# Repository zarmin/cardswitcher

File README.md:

# Card switcher

In some cases physical switching of a smart card is required to operate / test a system, this project can change between multiple smart cards electronically.

The device can be managed via a USB interface (Serial bus over USB).

_The project is inspired by [Smart Card removinator project](https://github.com/nkinder/smart-card-removinator)._

# Hardware

The device is made up from 3 different components: card shield, card controller, card adapter

## Card shield

One device installation can use multiple card shields, one card shield can take one card. The maximum number of stackable card shields are 15 (or 16, but w/o a unselected option). These shields are vertically stacked pcb modules.

Every shield have a 4 bit address, which can be changed by a dip switch on the board (the space between the stacked modules are enough to change the address after it stacked with a tweezer). The controller can detect address collisions via a feedback resistor.

Card shields can't detect if they have an inserted card or not.

### Card shield schematics

### Card shield PCB

### Card shield photos

## Card controller

One device installation needs one controller. The controller will the base of the card shields.

The card controller can be controller (and powered) via mini USB. It connects to the card adapter with a ethernet cable (but not ethernet protocol of course).

It has an IC socket, initially designed to hold an ATMEGA168PA, with an Arduino software. The board also has a ISP connector to program the MCU.

### Card controller schematics

### Card controller PCB

### Card controller photos

## Card adapter

The card adapter is the _fake_ card, that goes into the real card slot.

### Card adapter PCB

### Card adapter photos

# Software

Software is in the mcu-software folder as an Arduino project. It can be uploaded via the USB interface or via the ISP. For the development the MiniCore Arduino board library used for the ATMega168IC (16 Mhz external clock; 168P / 168PA variant).

The software is checking the available card shield addresses upon boot and refuse to start (reboot loop with fast blinking of the activity LED) if an address collision is detected.
After the boot, it can be controlled via serial (via USB), by writing the addresses in ASCII (no newline required).

# Photos

_Installation with two card shield modules and cards_

## Example terminal communication

```
Serial init
Device found on address: 1
Device found on address: 2
Ready to use!
Address? >>
Set to address (no active device): 4
Address? >>
Set to address (active device): 1
Address? >>
Set to address (active device): 2
Address? >>
```

# Components

The EAGLE files are containing the required components numbers (extra component libraries also included).

Special (non common / passive) components are:
- card shield: 2x SN74HC4066DR Quadruple Bilateral Analog Switch
- card shield: 1x CD74HC85M CMOS Logic 4-Bit Magnitude Comparator
- card shield: 1x C702 10M008 230 40 Amphenol Tuchel Smard card connector (Mouser)
- card controller: 1x FT232BL FTDI IC
- card controller: 1x ATMEGA168PA MCU

Every other component can be found in bom folder, or can be exported from EAGLE files.

# Isolation

The device using a common fused (500 mA) ground between the USB and the smart card adapter (Smart card connector GND). 

If complete isolation is required then an USB isolator (eg. Adafruit USB Isolator) can be used. The device should draw under 80 mA.

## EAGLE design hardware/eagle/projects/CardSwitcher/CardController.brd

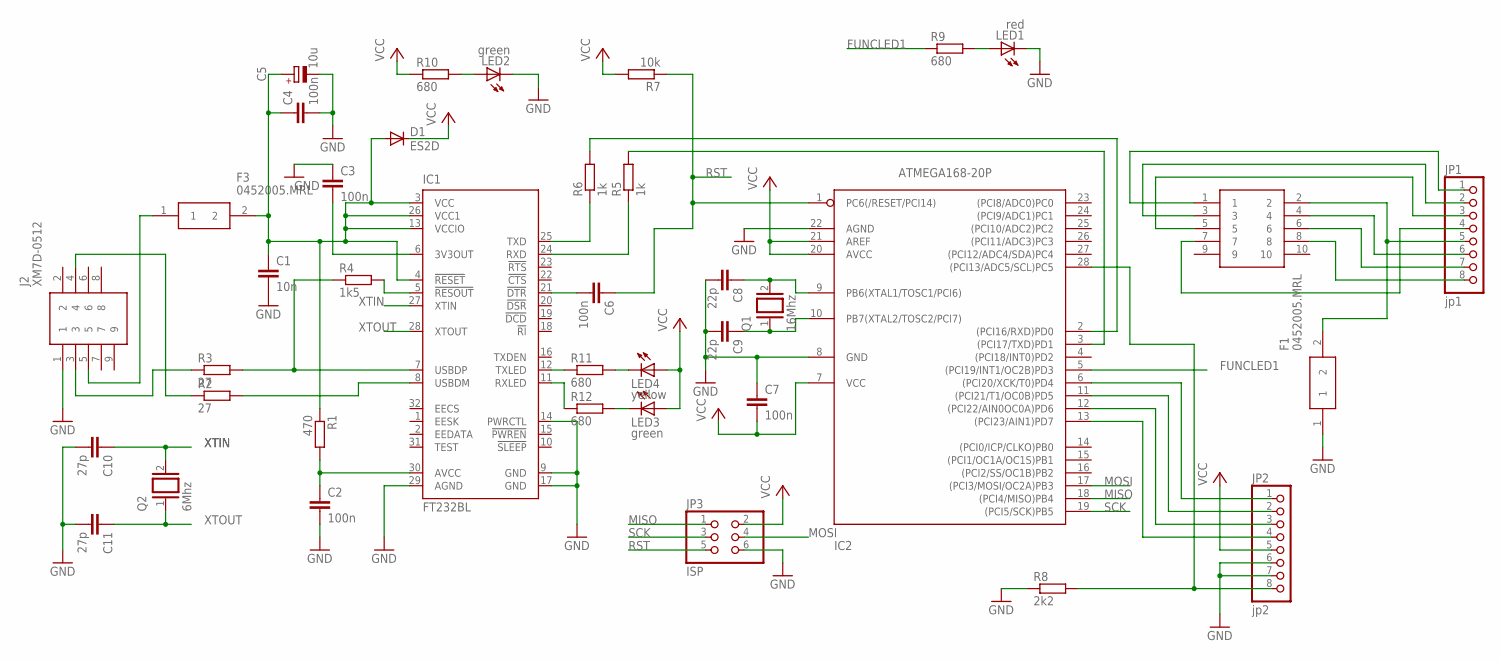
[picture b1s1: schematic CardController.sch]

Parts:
C1: 10n; C1206
C2, C3, C4, C6, C7: 100n; C1206
C5: 10u; B/3528-21W
C8, C9: 22p; C1206
C10, C11: 27p; C1206
D1: ES2D; SMB
F1, F3: 0452005.MRL; FUSC6127X294N
IC1: FT232BL; LQFP32-7X7
IC2: ATMEGA168-20P; DIL28-3
J1: 615008140121
J2: XM7D-0512; XM7D0512
JP1: jp1; 1X08
JP2: jp2; 1X08
JP3: ISP; 2X03
LED1: red; SML1206
LED2, LED3: green; SML1206
LED4: yellow; SML1206
Q1: 16Mhz; QS
Q2: 6Mhz; QS
R1: 470; R0805
R2, R3: 27; R0805
R4: 1k5; R0805
R5, R6: 1k; R0805
R7: 10k; R0805
R8: 2k2; R0805
R9, R10, R11, R12: 680; R0805

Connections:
FUNCLED1: IC2.5 ((PCI19/INT1/OC2B)PD3), R9.1
GND: C1.2, C2.2, C3.1, C4.2, C5.-, C7.1, C8.2, C9.2, C10.2, C11.2, F1.1, IC1.9 (GND), IC1.14 (PWRCTL), IC1.17 (GND), IC1.29 (AGND), IC2.8 (GND), IC2.22 (AGND), J2.1, JP2.6, JP2.7, JP3.6, LED1.C, LED2.C, R8.1
MISO: IC2.18 ((PCI4/MISO)PB4), JP3.1
MOSI: IC2.17 ((PCI3/MOSI/OC2A)PB3), JP3.4
unnamed: F3.1, J2.5
unnamed: C1.1, C4.1, C5.+, D1.A, F3.2, IC1.3 (VCC), IC1.4 (!RESET), IC1.13 (VCCIO), IC1.26 (VCC1), R1.1
unnamed: C2.1, IC1.30 (AVCC), R1.2
unnamed: C3.2, IC1.6 (3V3OUT)
unnamed: J2.4, R2.1
unnamed: IC1.8 (USBDM), R2.2
unnamed: J1.3, JP1.2
unnamed: IC1.5 (!RESOUT), R4.2
unnamed: IC1.25 (TXD), R6.1
unnamed: IC2.2 ((PCI16/RXD)PD0), R6.2
unnamed: IC2.13 ((PCI23/AIN1)PD7), JP2.4
unnamed: IC1.24 (RXD), R5.1
unnamed: C6.2, IC1.21 (!DTR)
unnamed: IC2.12 ((PCI22/AIN0OC0A)PD6), JP2.3
unnamed: C8.1, IC2.9 (PB6(XTAL1/TOSC1/PCI6)), Q1.2
unnamed: C9.1, IC2.10 (PB7(XTAL2/TOSC2/PCI7)), Q1.1
unnamed: IC2.28 ((PCI13/ADC5/SCL)PC5), JP2.8, R8.2
unnamed: IC1.12 (TXLED), R11.1
unnamed: LED1.A, R9.2
unnamed: J1.1, JP1.1
unnamed: IC2.3 ((PCI17/TXD)PD1), R5.2
unnamed: IC2.11 ((PCI21/T1/OC0B)PD5), JP2.2
unnamed: IC2.6 ((PCI20/XCK/T0)PD4), JP2.1
unnamed: J1.5, JP1.3
unnamed: J1.7, JP1.4
unnamed: F1.2, J1.2, JP1.5
unnamed: J1.4, JP1.6
unnamed: J1.6, JP1.7
unnamed: J1.8, JP1.8
unnamed: J2.3, R3.1
unnamed: LED2.A, R10.2
unnamed: IC1.11 (RXLED), R12.1
unnamed: LED4.C, R11.2
unnamed: LED3.C, R12.2
unnamed: IC1.7 (USBDP), R3.2, R4.1
RST: C6.1, IC2.1 (PC6(/RESET/PCI14)), JP3.5, R7.1
SCK: IC2.19 ((PCI5/SCK)PB5), JP3.3
VCC: C7.2, D1.C, IC2.7 (VCC), IC2.20 (AVCC), IC2.21 (AREF), JP2.5, JP3.2, LED3.A, LED4.A, R7.2, R10.1
XTIN: C10.1, IC1.27 (XTIN), Q2.2
XTOUT: C11.1, IC1.28 (XTOUT), Q2.1

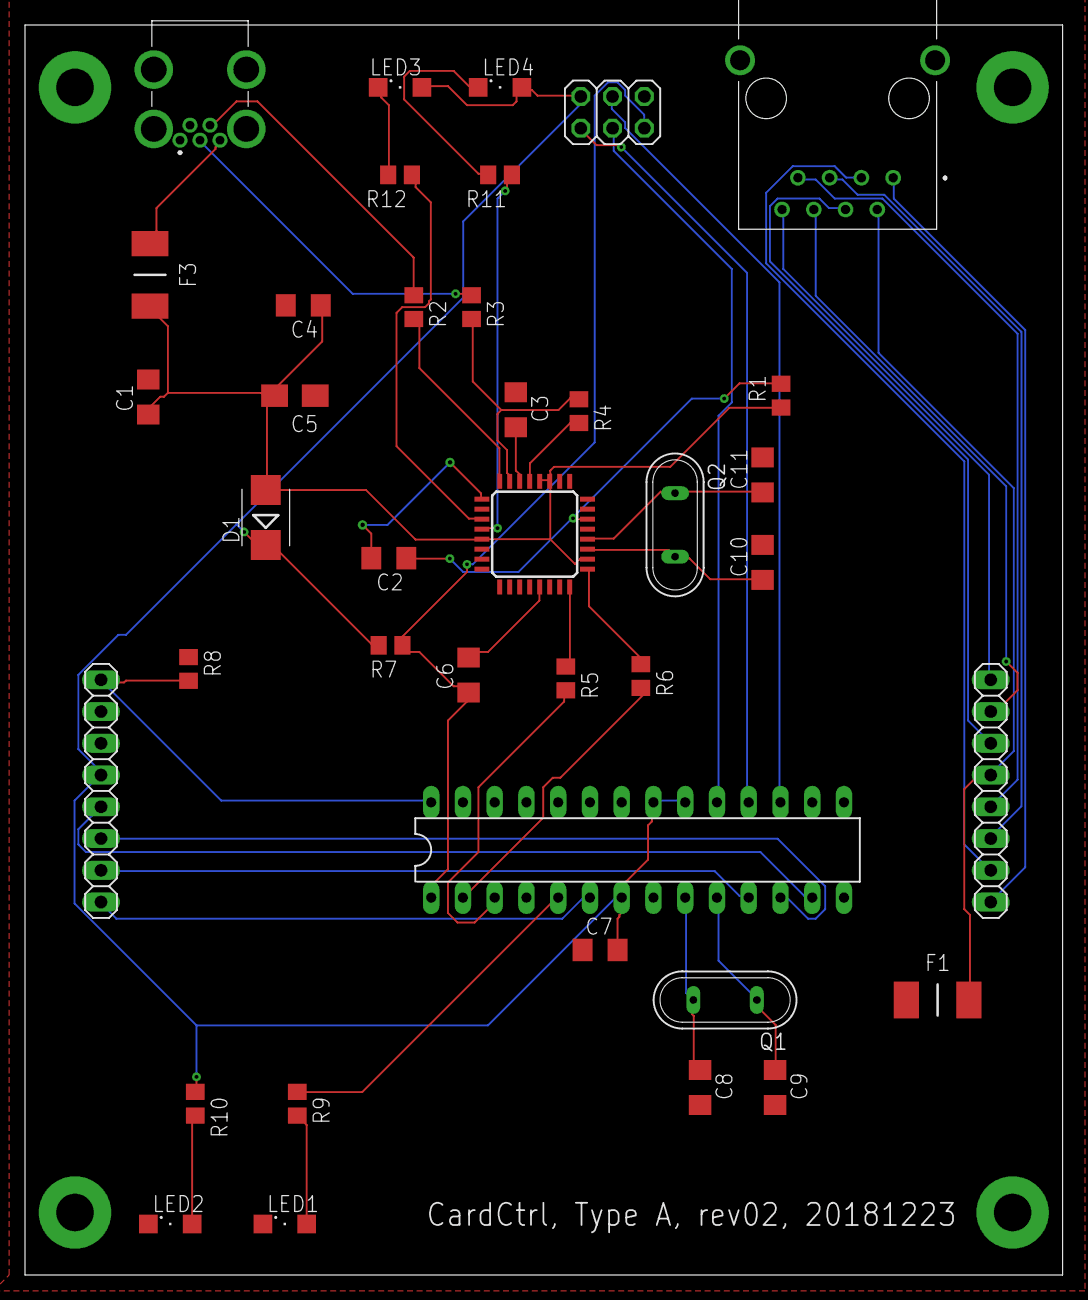
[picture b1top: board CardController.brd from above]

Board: 2 copper layers, 83.0 x 100.0 mm, 39 parts (0 on the bottom side), 44 nets.

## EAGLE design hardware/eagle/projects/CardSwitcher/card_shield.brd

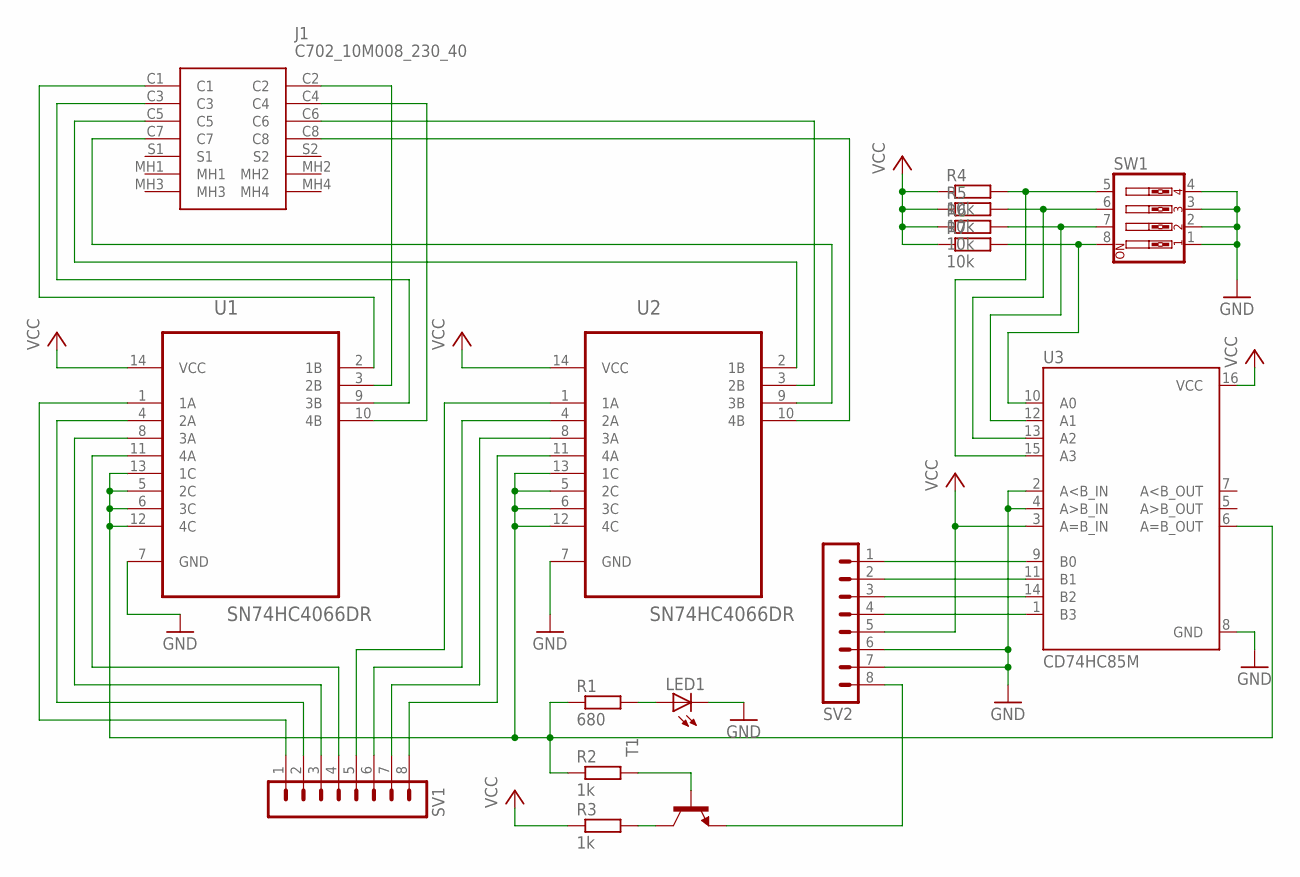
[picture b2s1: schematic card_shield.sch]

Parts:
J1: C702_10M008_230_40; C70210M00823040
LED1: LEDSML1206; SML1206
R1: 680; R0805
R2, R3: 1k; R0805
R4, R5, R6, R7: 10k; R0805
SV1, SV2: MA08-1
SW1: SW_DIP-4; EDG-04
T1: BC817-16-NPN-SOT23-BEC; SOT23-BEC
U1, U2: SN74HC4066DR; SOIC127P600X175-14N
U3: CD74HC85M; SOIC12P600X175-16N

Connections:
GND: LED1.C, SV2.6, SV2.7, SW1.1, SW1.2, SW1.3, SW1.4, U1.7 (GND), U2.7 (GND), U3.2 (A<B_IN), U3.4 (A>B_IN), U3.8 (GND)
unnamed: J1.C1, U1.2 (1B)
unnamed: J1.C3, U1.9 (3B)
unnamed: J1.C2, U1.3 (2B)
unnamed: J1.C4, U1.10 (4B)
unnamed: J1.C5, U2.2 (1B)
unnamed: J1.C6, U2.3 (2B)
unnamed: J1.C7, U2.9 (3B)
unnamed: J1.C8, U2.10 (4B)
unnamed: SV1.1, U1.1 (1A)
unnamed: SV1.2, U1.4 (2A)
unnamed: SV1.3, U1.8 (3A)
unnamed: SV1.4, U1.11 (4A)
unnamed: SV1.5, U2.1 (1A)
unnamed: SV1.6, U2.4 (2A)
unnamed: SV1.7, U2.8 (3A)
unnamed: SV1.8, U2.11 (4A)
unnamed: R1.1, R2.1, U1.5 (2C), U1.6 (3C), U1.12 (4C), U1.13 (1C), U2.5 (2C), U2.6 (3C), U2.12 (4C), U2.13 (1C), U3.6 (A=B_OUT)
unnamed: LED1.A, R1.2
unnamed: SV2.1, U3.9 (B0)
unnamed: R2.2, T1.B
unnamed: SV2.2, U3.11 (B1)
unnamed: SV2.3, U3.14 (B2)
unnamed: SV2.4, U3.1 (B3)
unnamed: R7.2, SW1.8, U3.10 (A0)
unnamed: R6.2, SW1.7, U3.12 (A1)
unnamed: R5.2, SW1.6, U3.13 (A2)
unnamed: R4.2, SW1.5, U3.15 (A3)
unnamed: R3.2, T1.C
unnamed: SV2.8, T1.E
VCC: R3.1, R4.1, R5.1, R6.1, R7.1, SV2.5, U1.14 (VCC), U2.14 (VCC), U3.3 (A=B_IN), U3.16 (VCC)

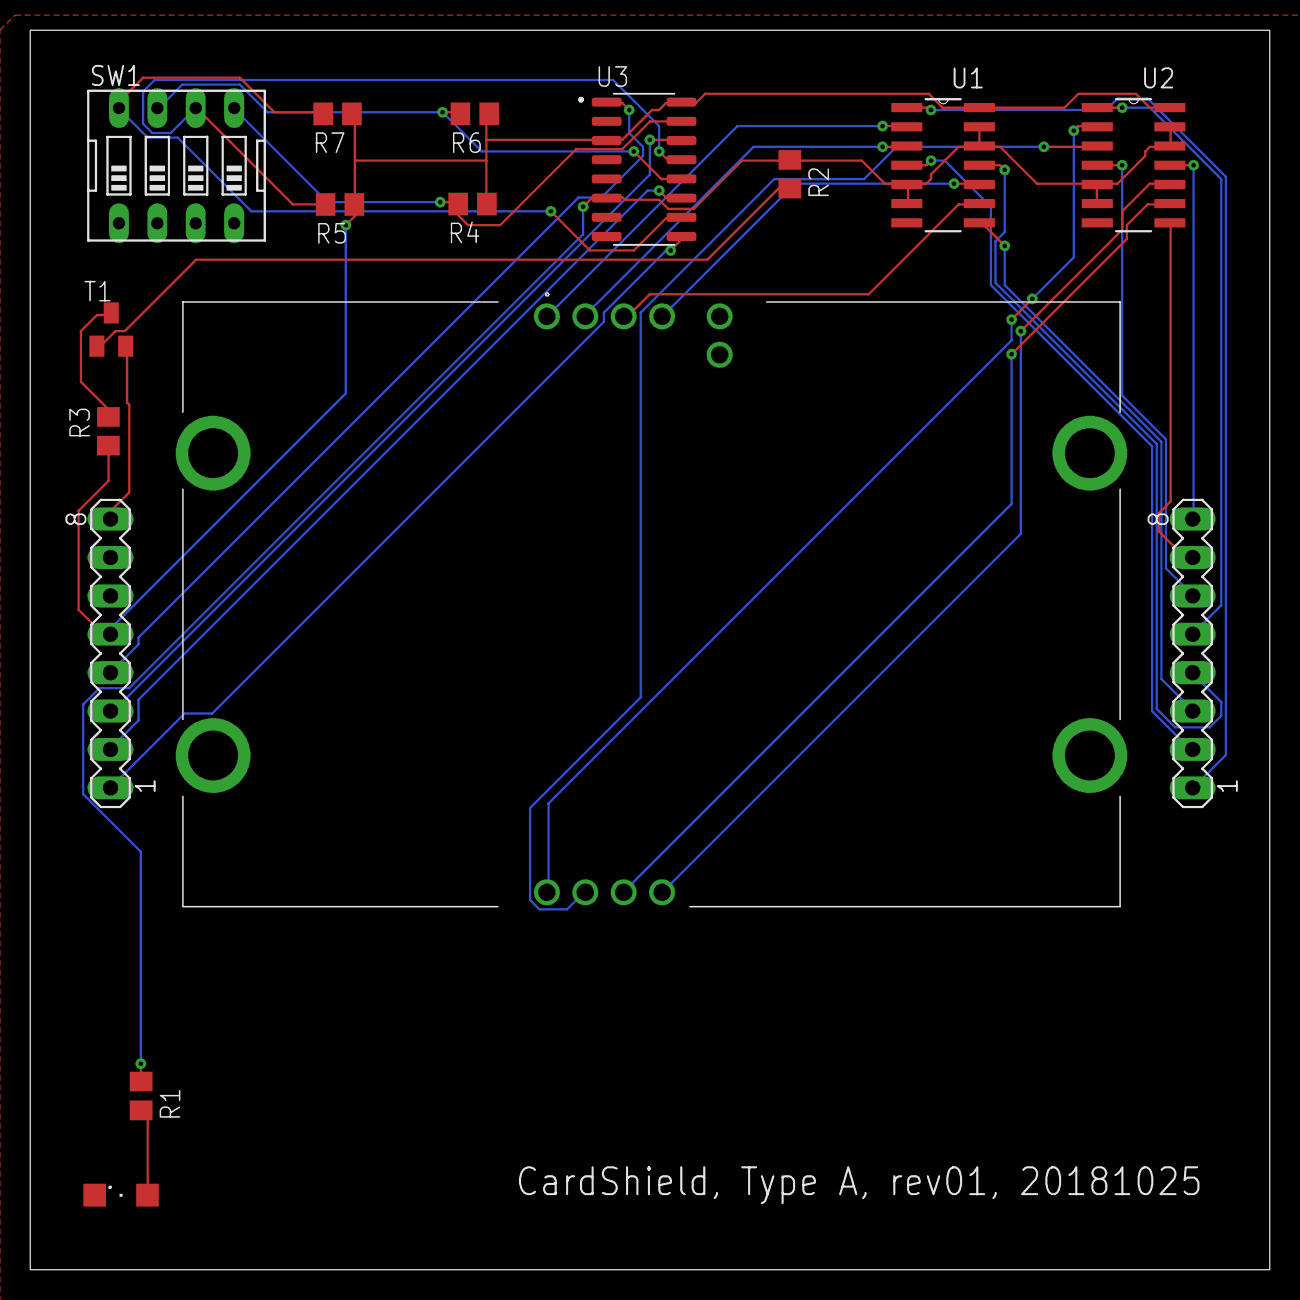
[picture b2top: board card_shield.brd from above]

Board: 2 copper layers, 82.0 x 82.0 mm, 16 parts (0 on the bottom side), 31 nets.

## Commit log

2019-01-14 eagle exported images added
2019-01-14 Readme updated
2019-01-14 BOM added
2019-01-14 photos added
2019-01-14 Serial read improved
2019-01-16 reset functionality added
